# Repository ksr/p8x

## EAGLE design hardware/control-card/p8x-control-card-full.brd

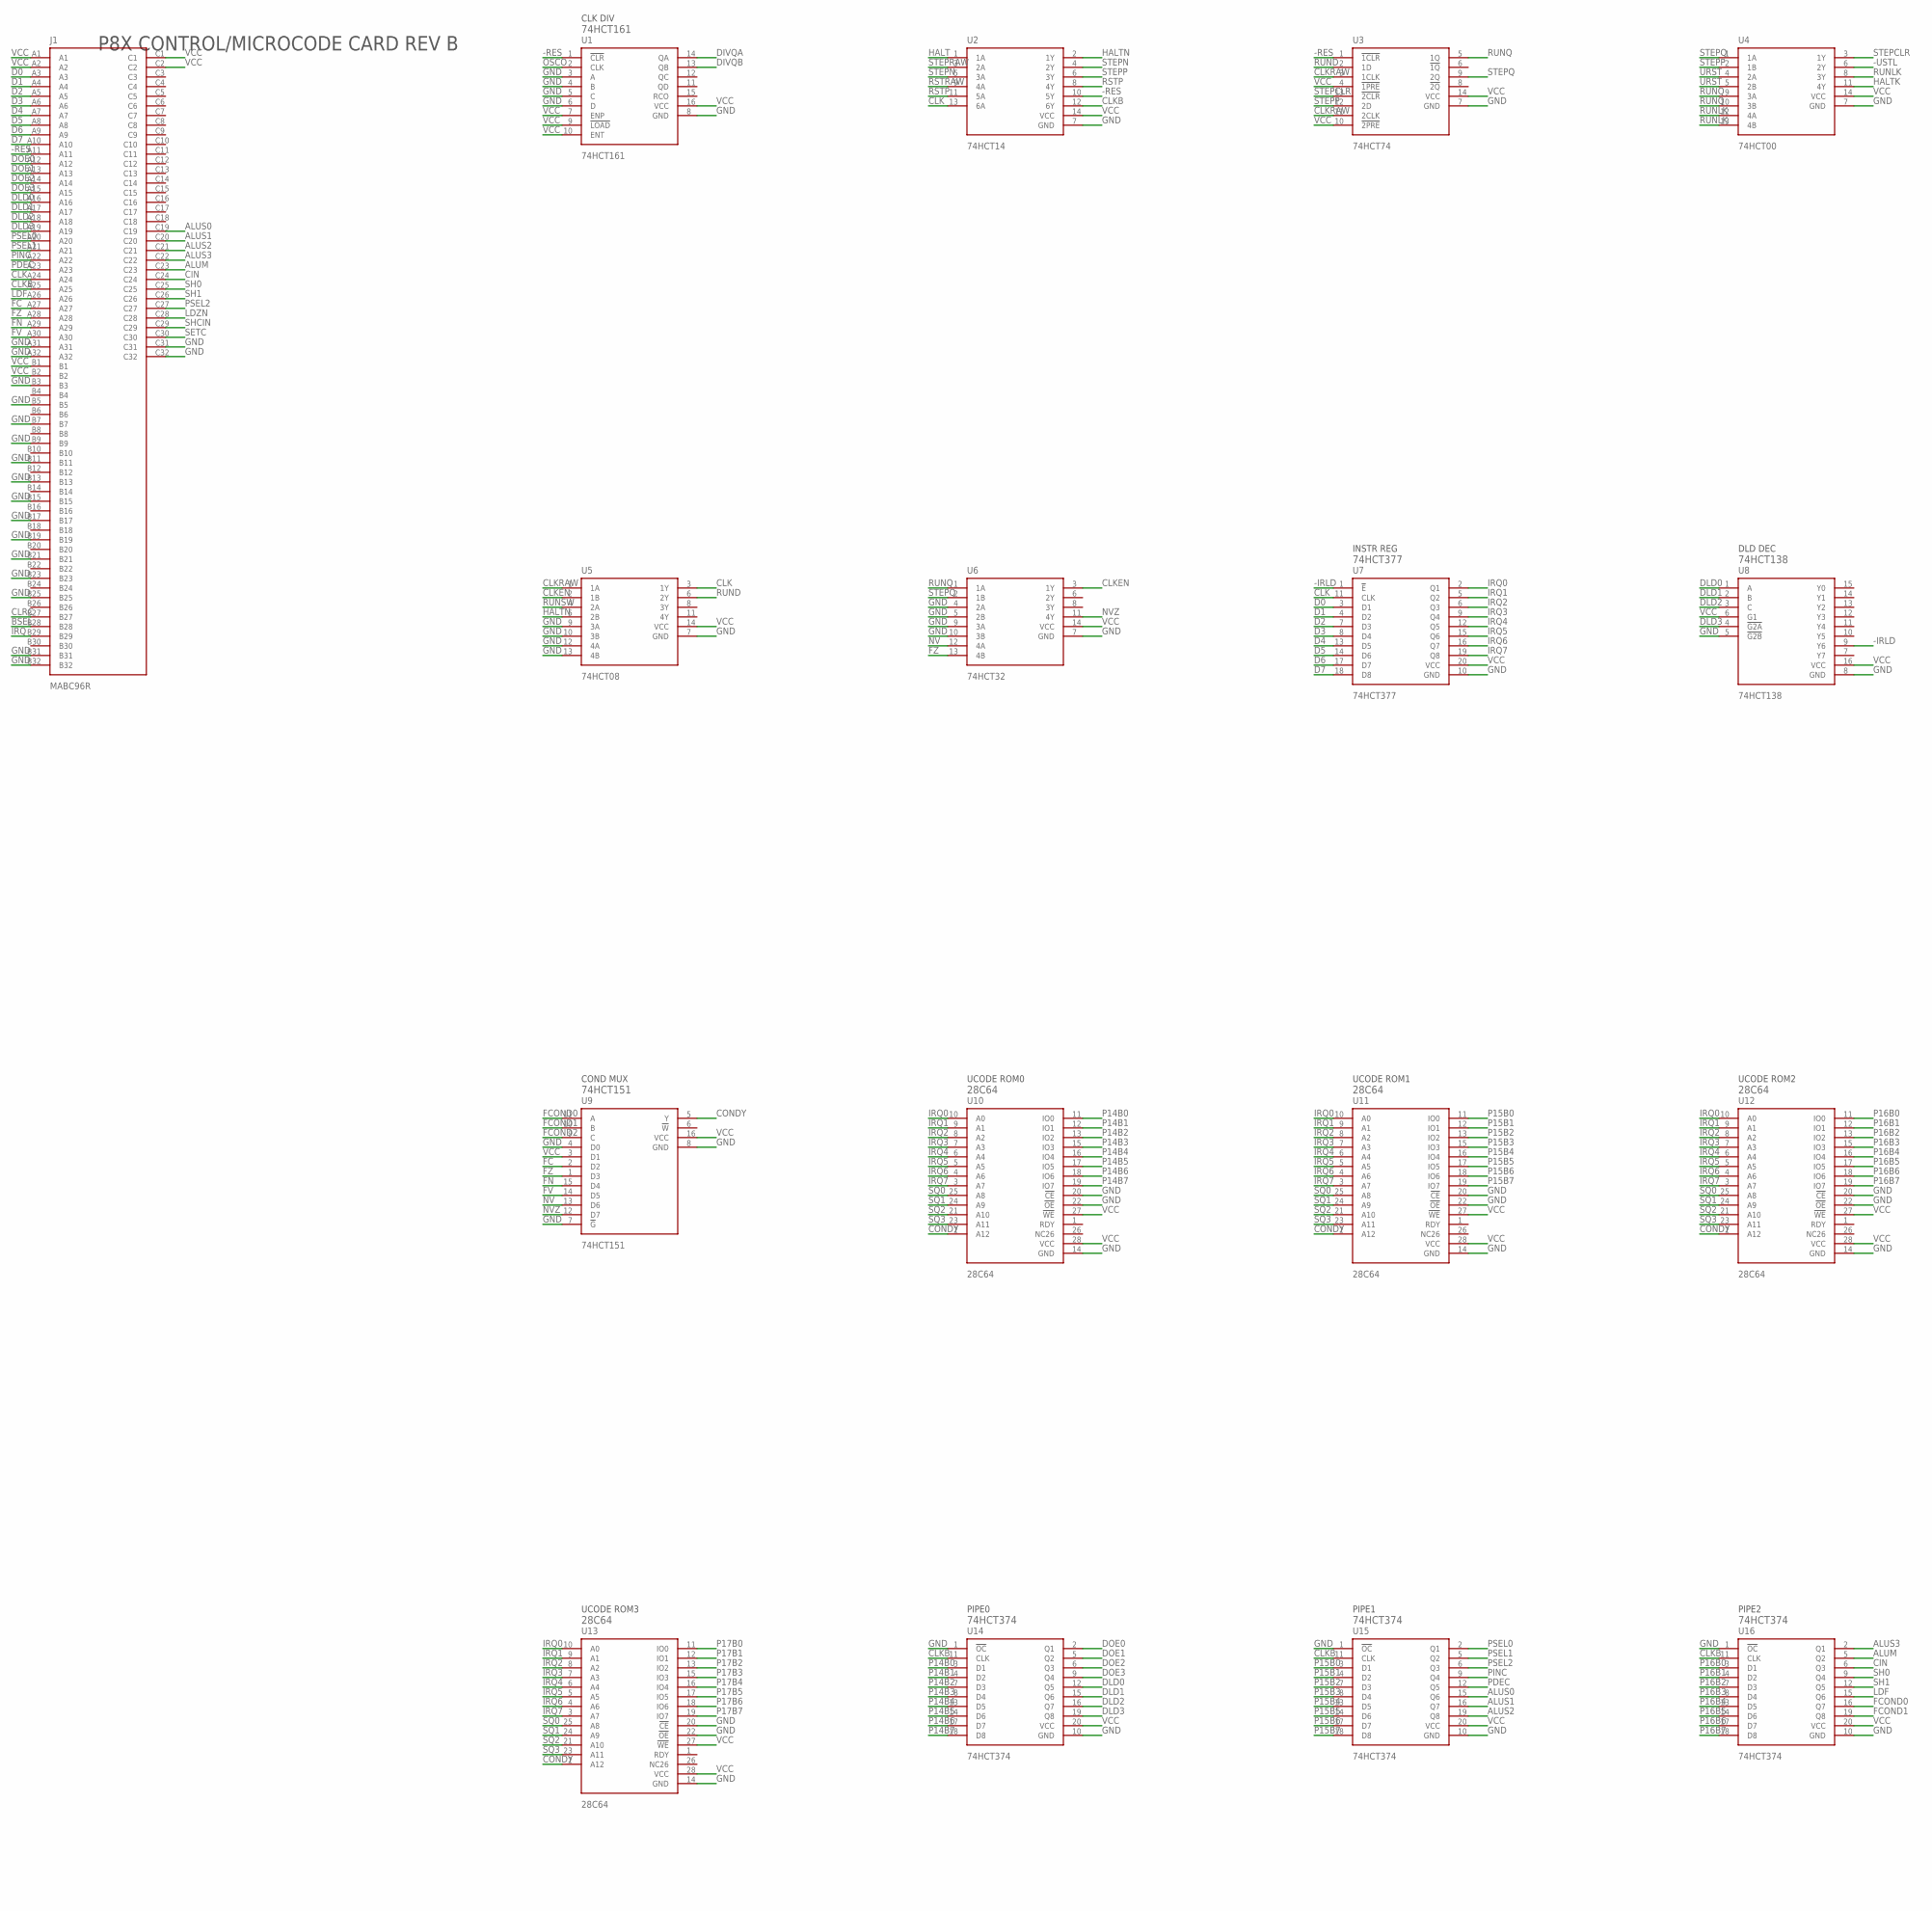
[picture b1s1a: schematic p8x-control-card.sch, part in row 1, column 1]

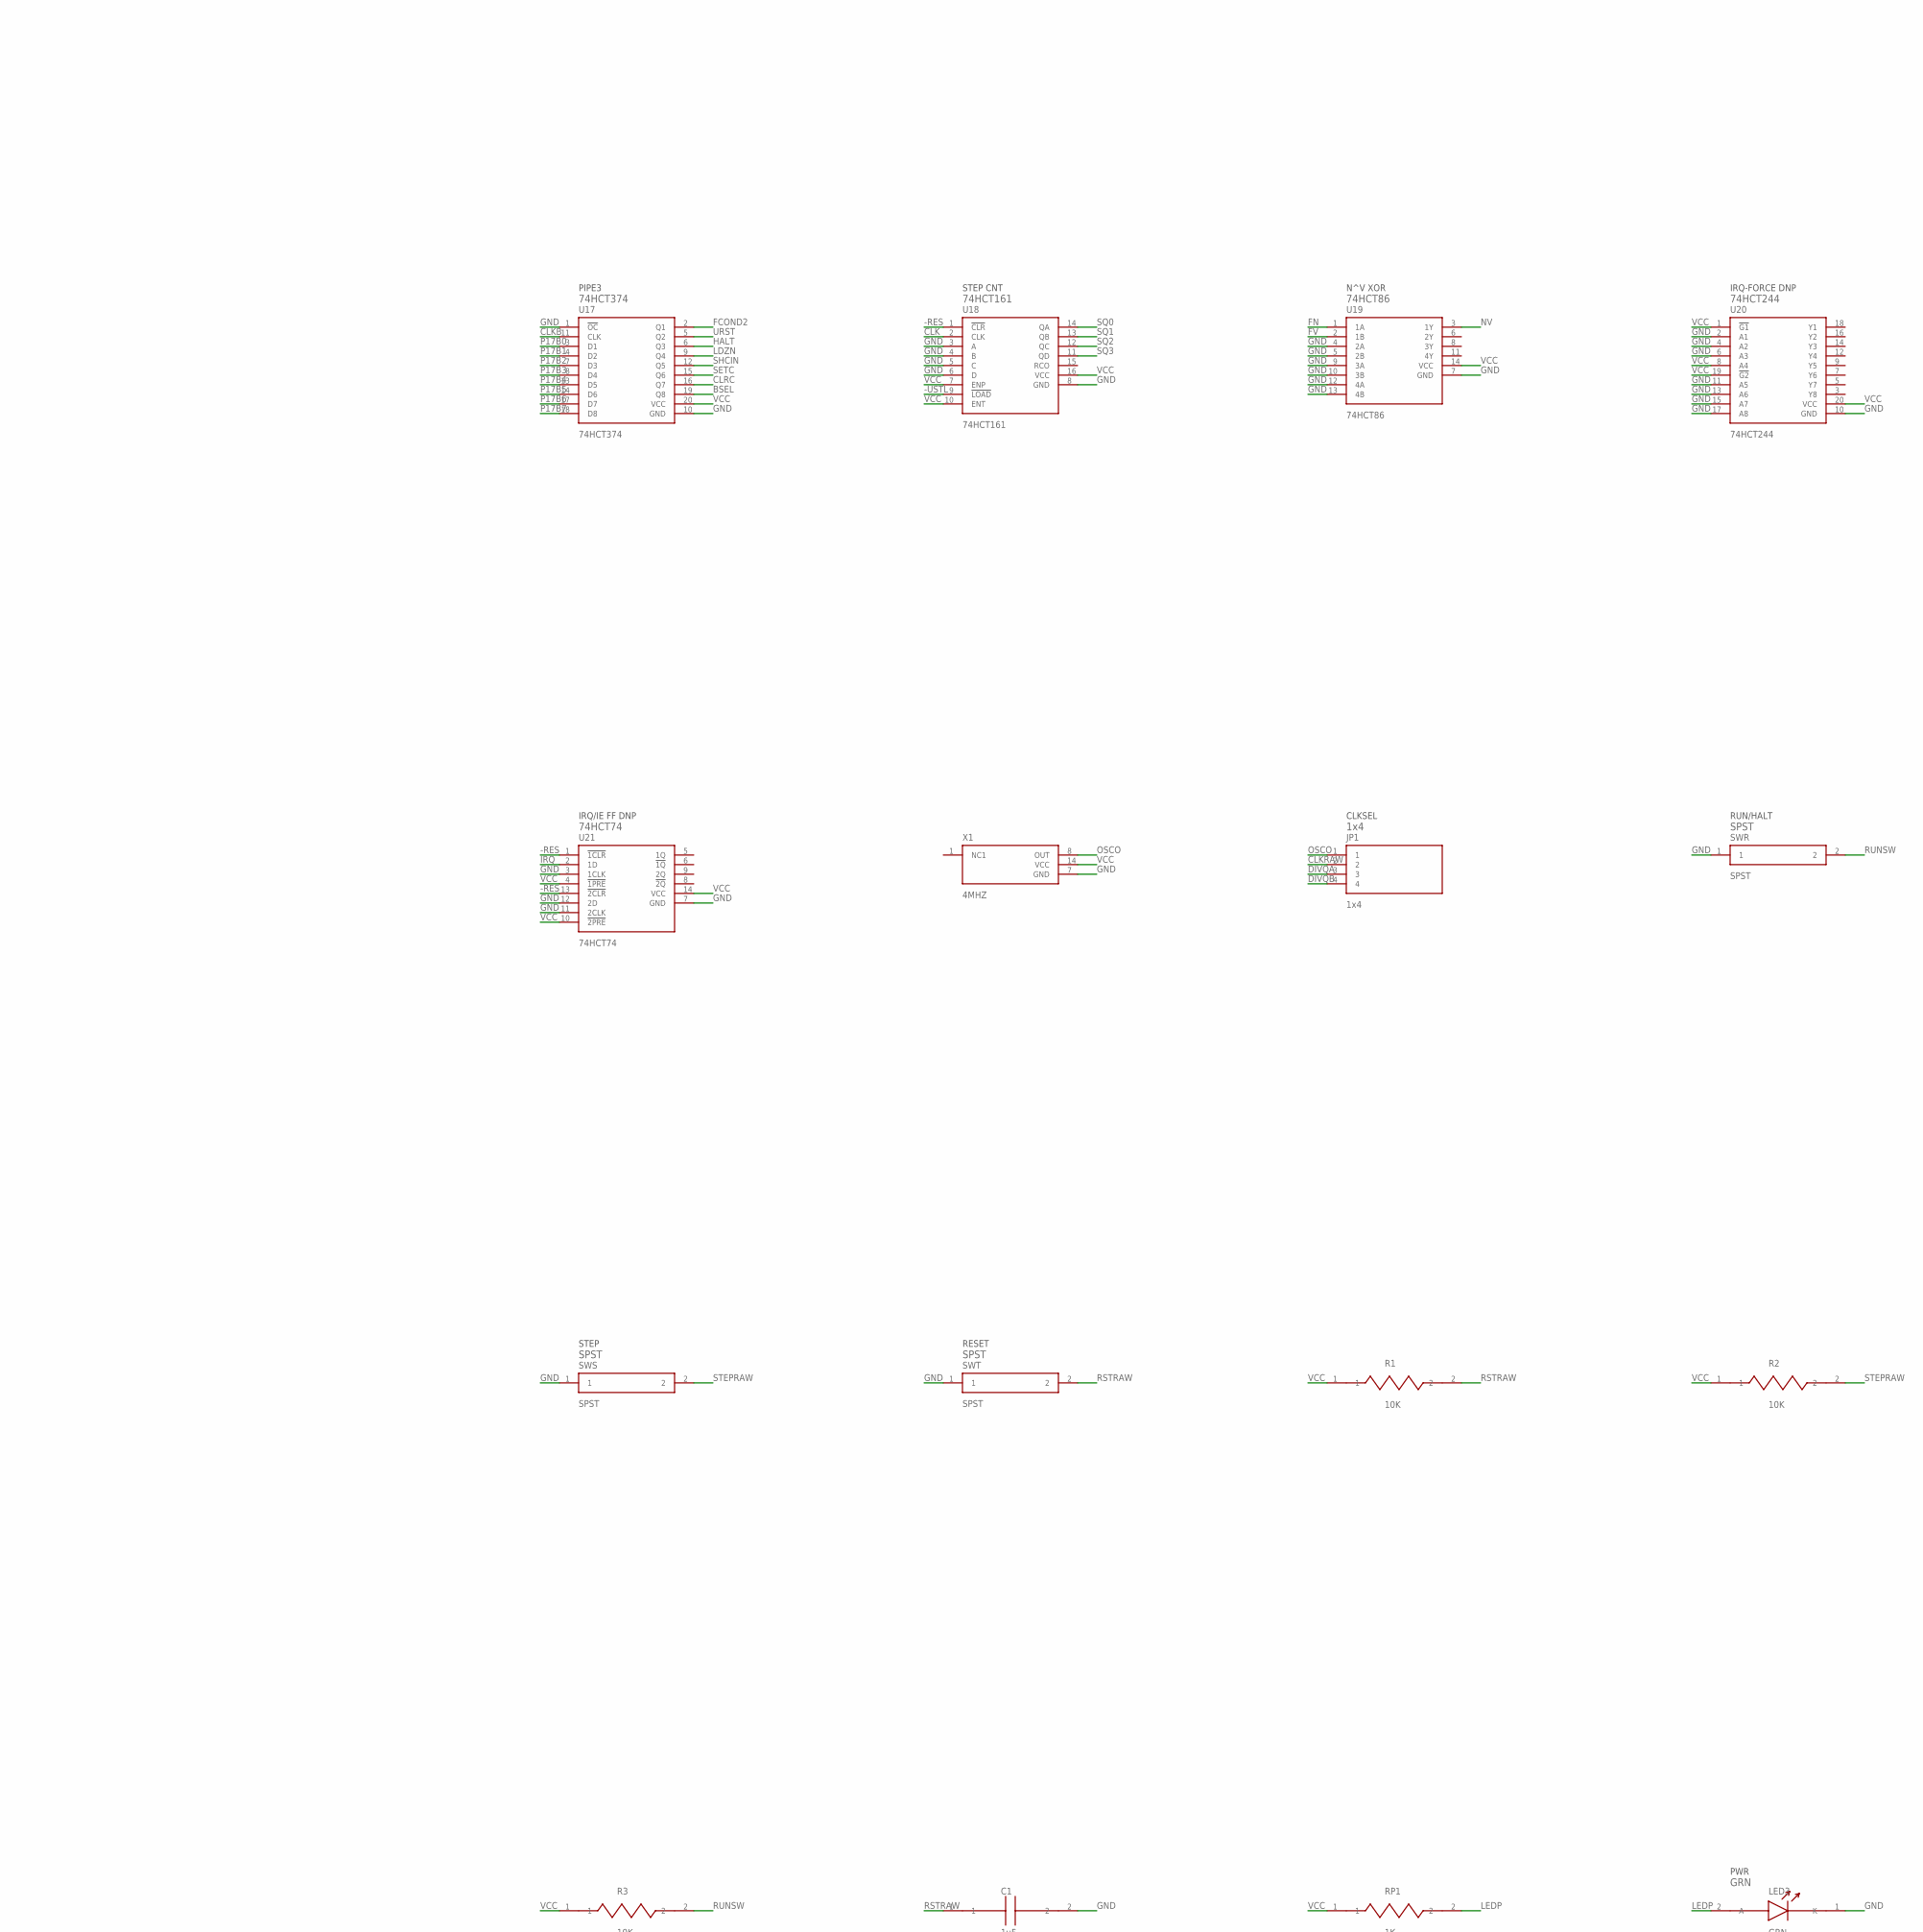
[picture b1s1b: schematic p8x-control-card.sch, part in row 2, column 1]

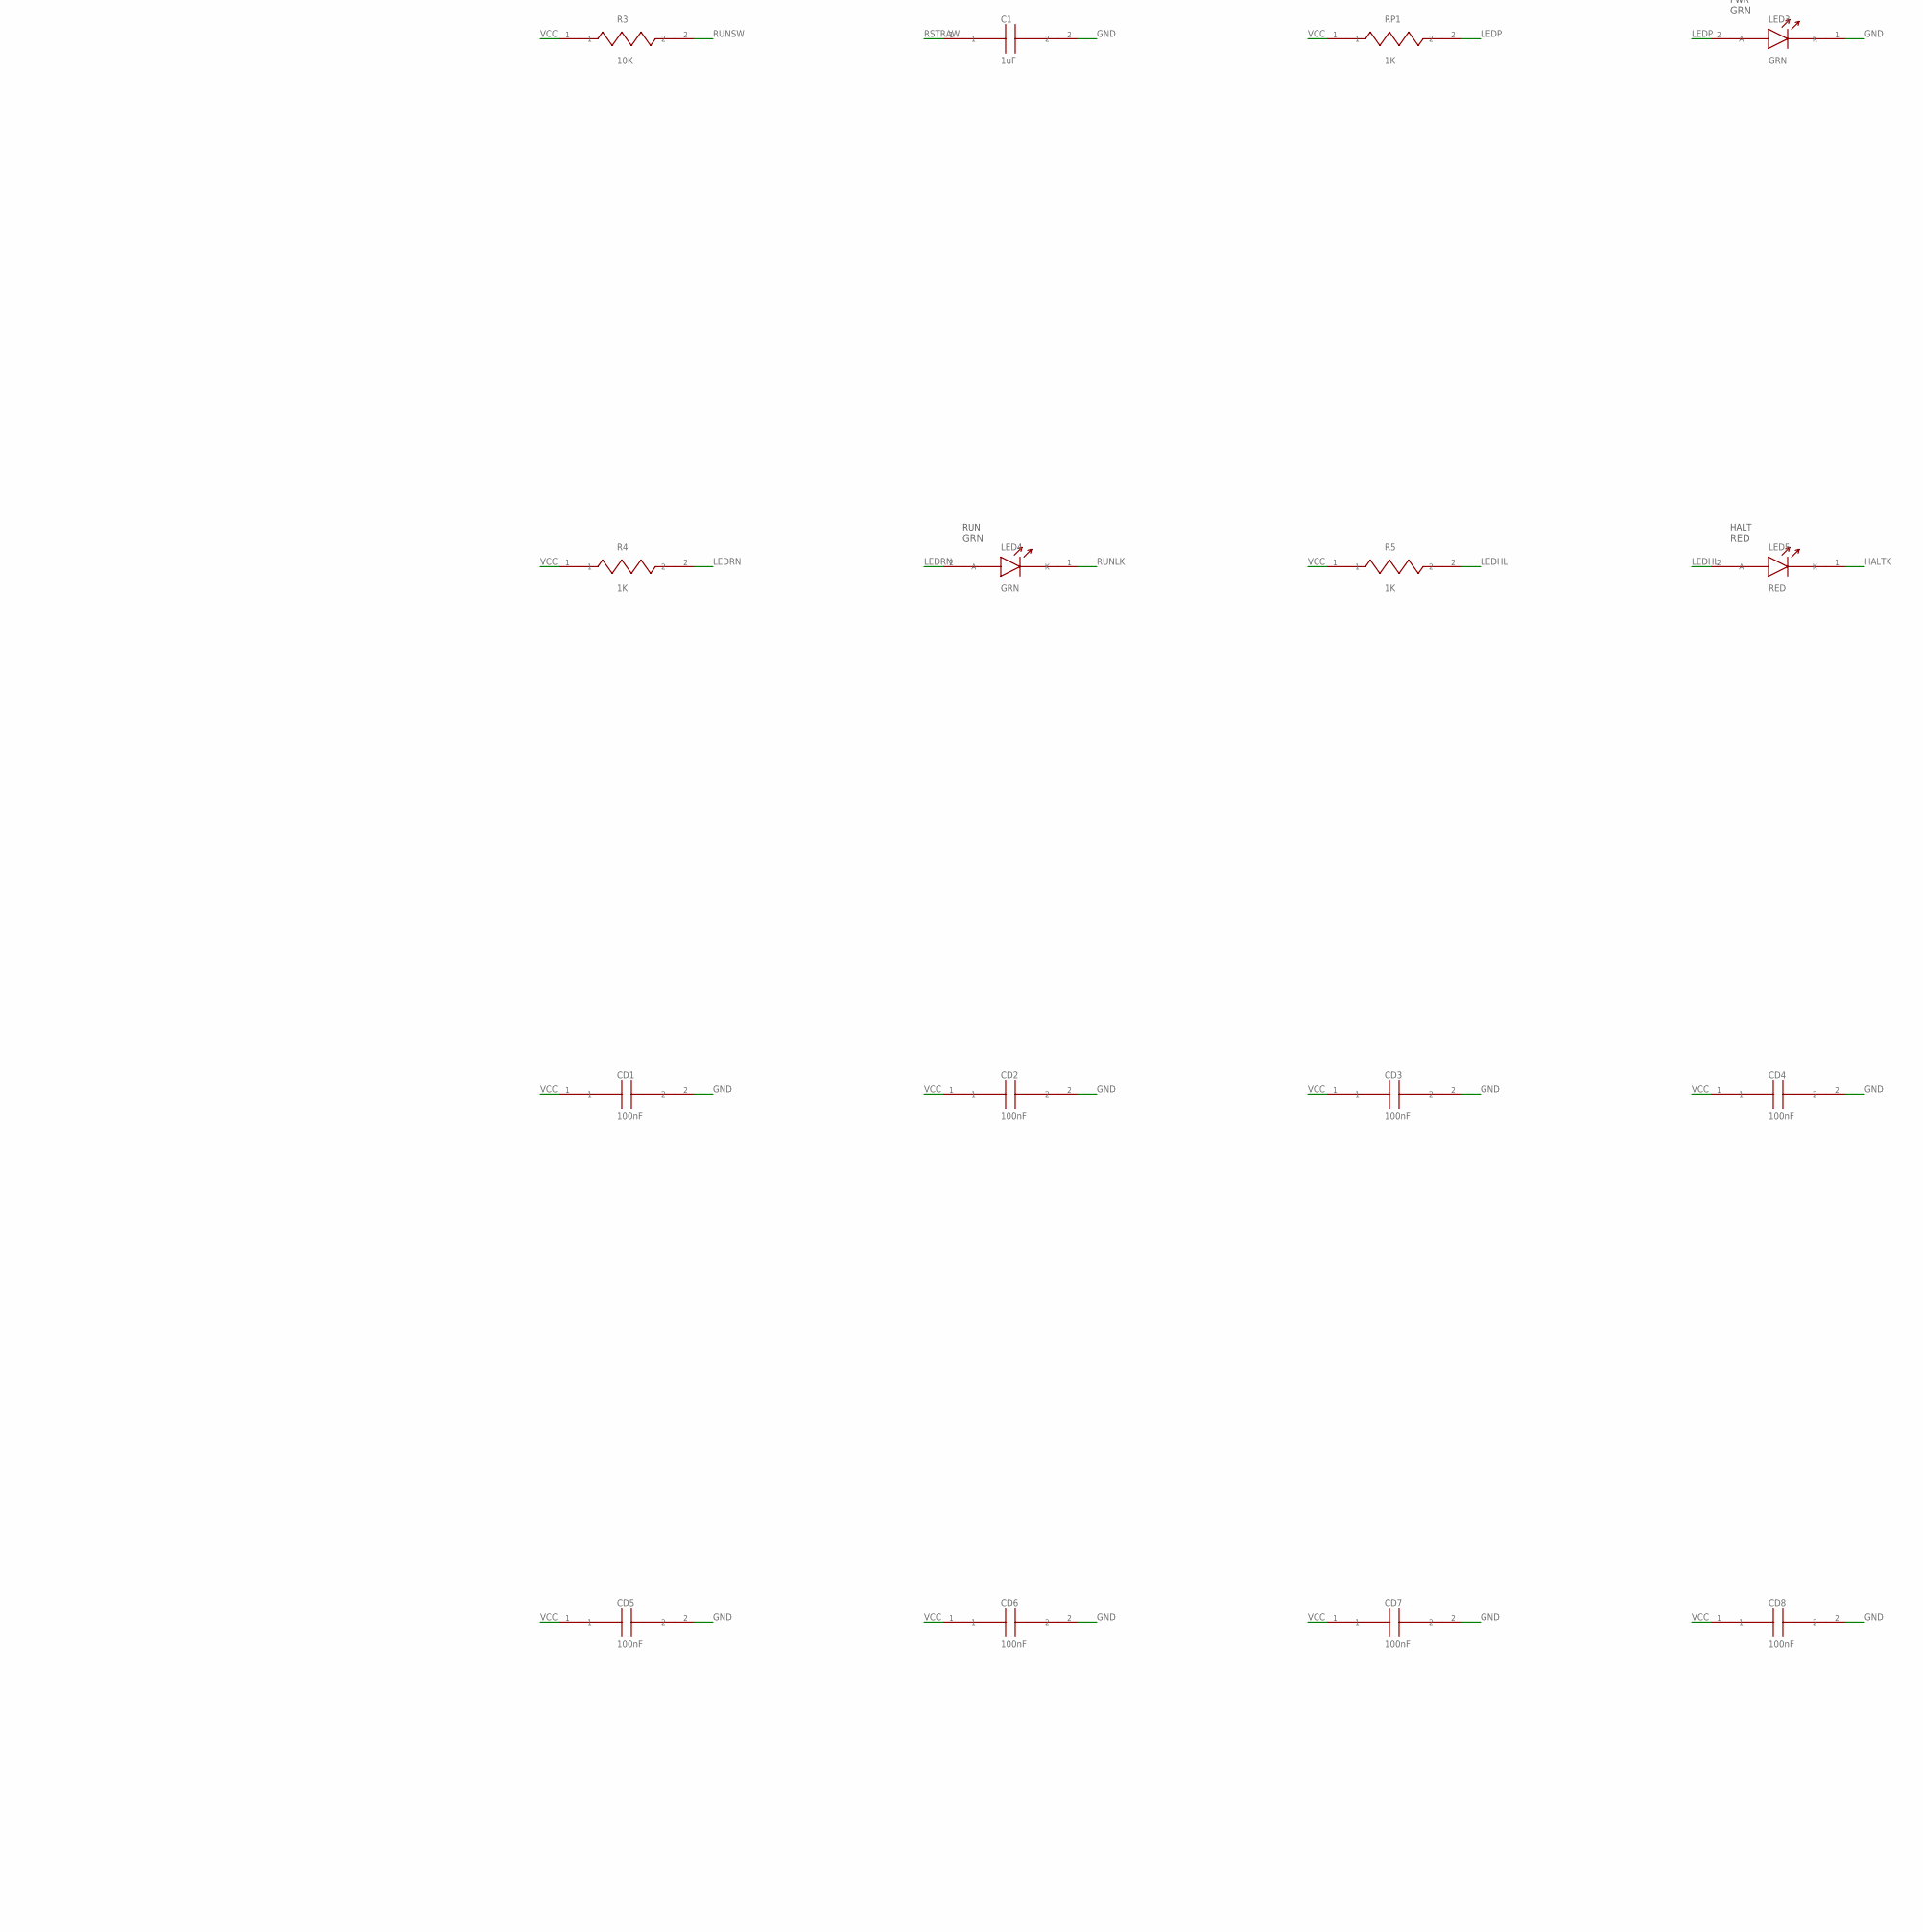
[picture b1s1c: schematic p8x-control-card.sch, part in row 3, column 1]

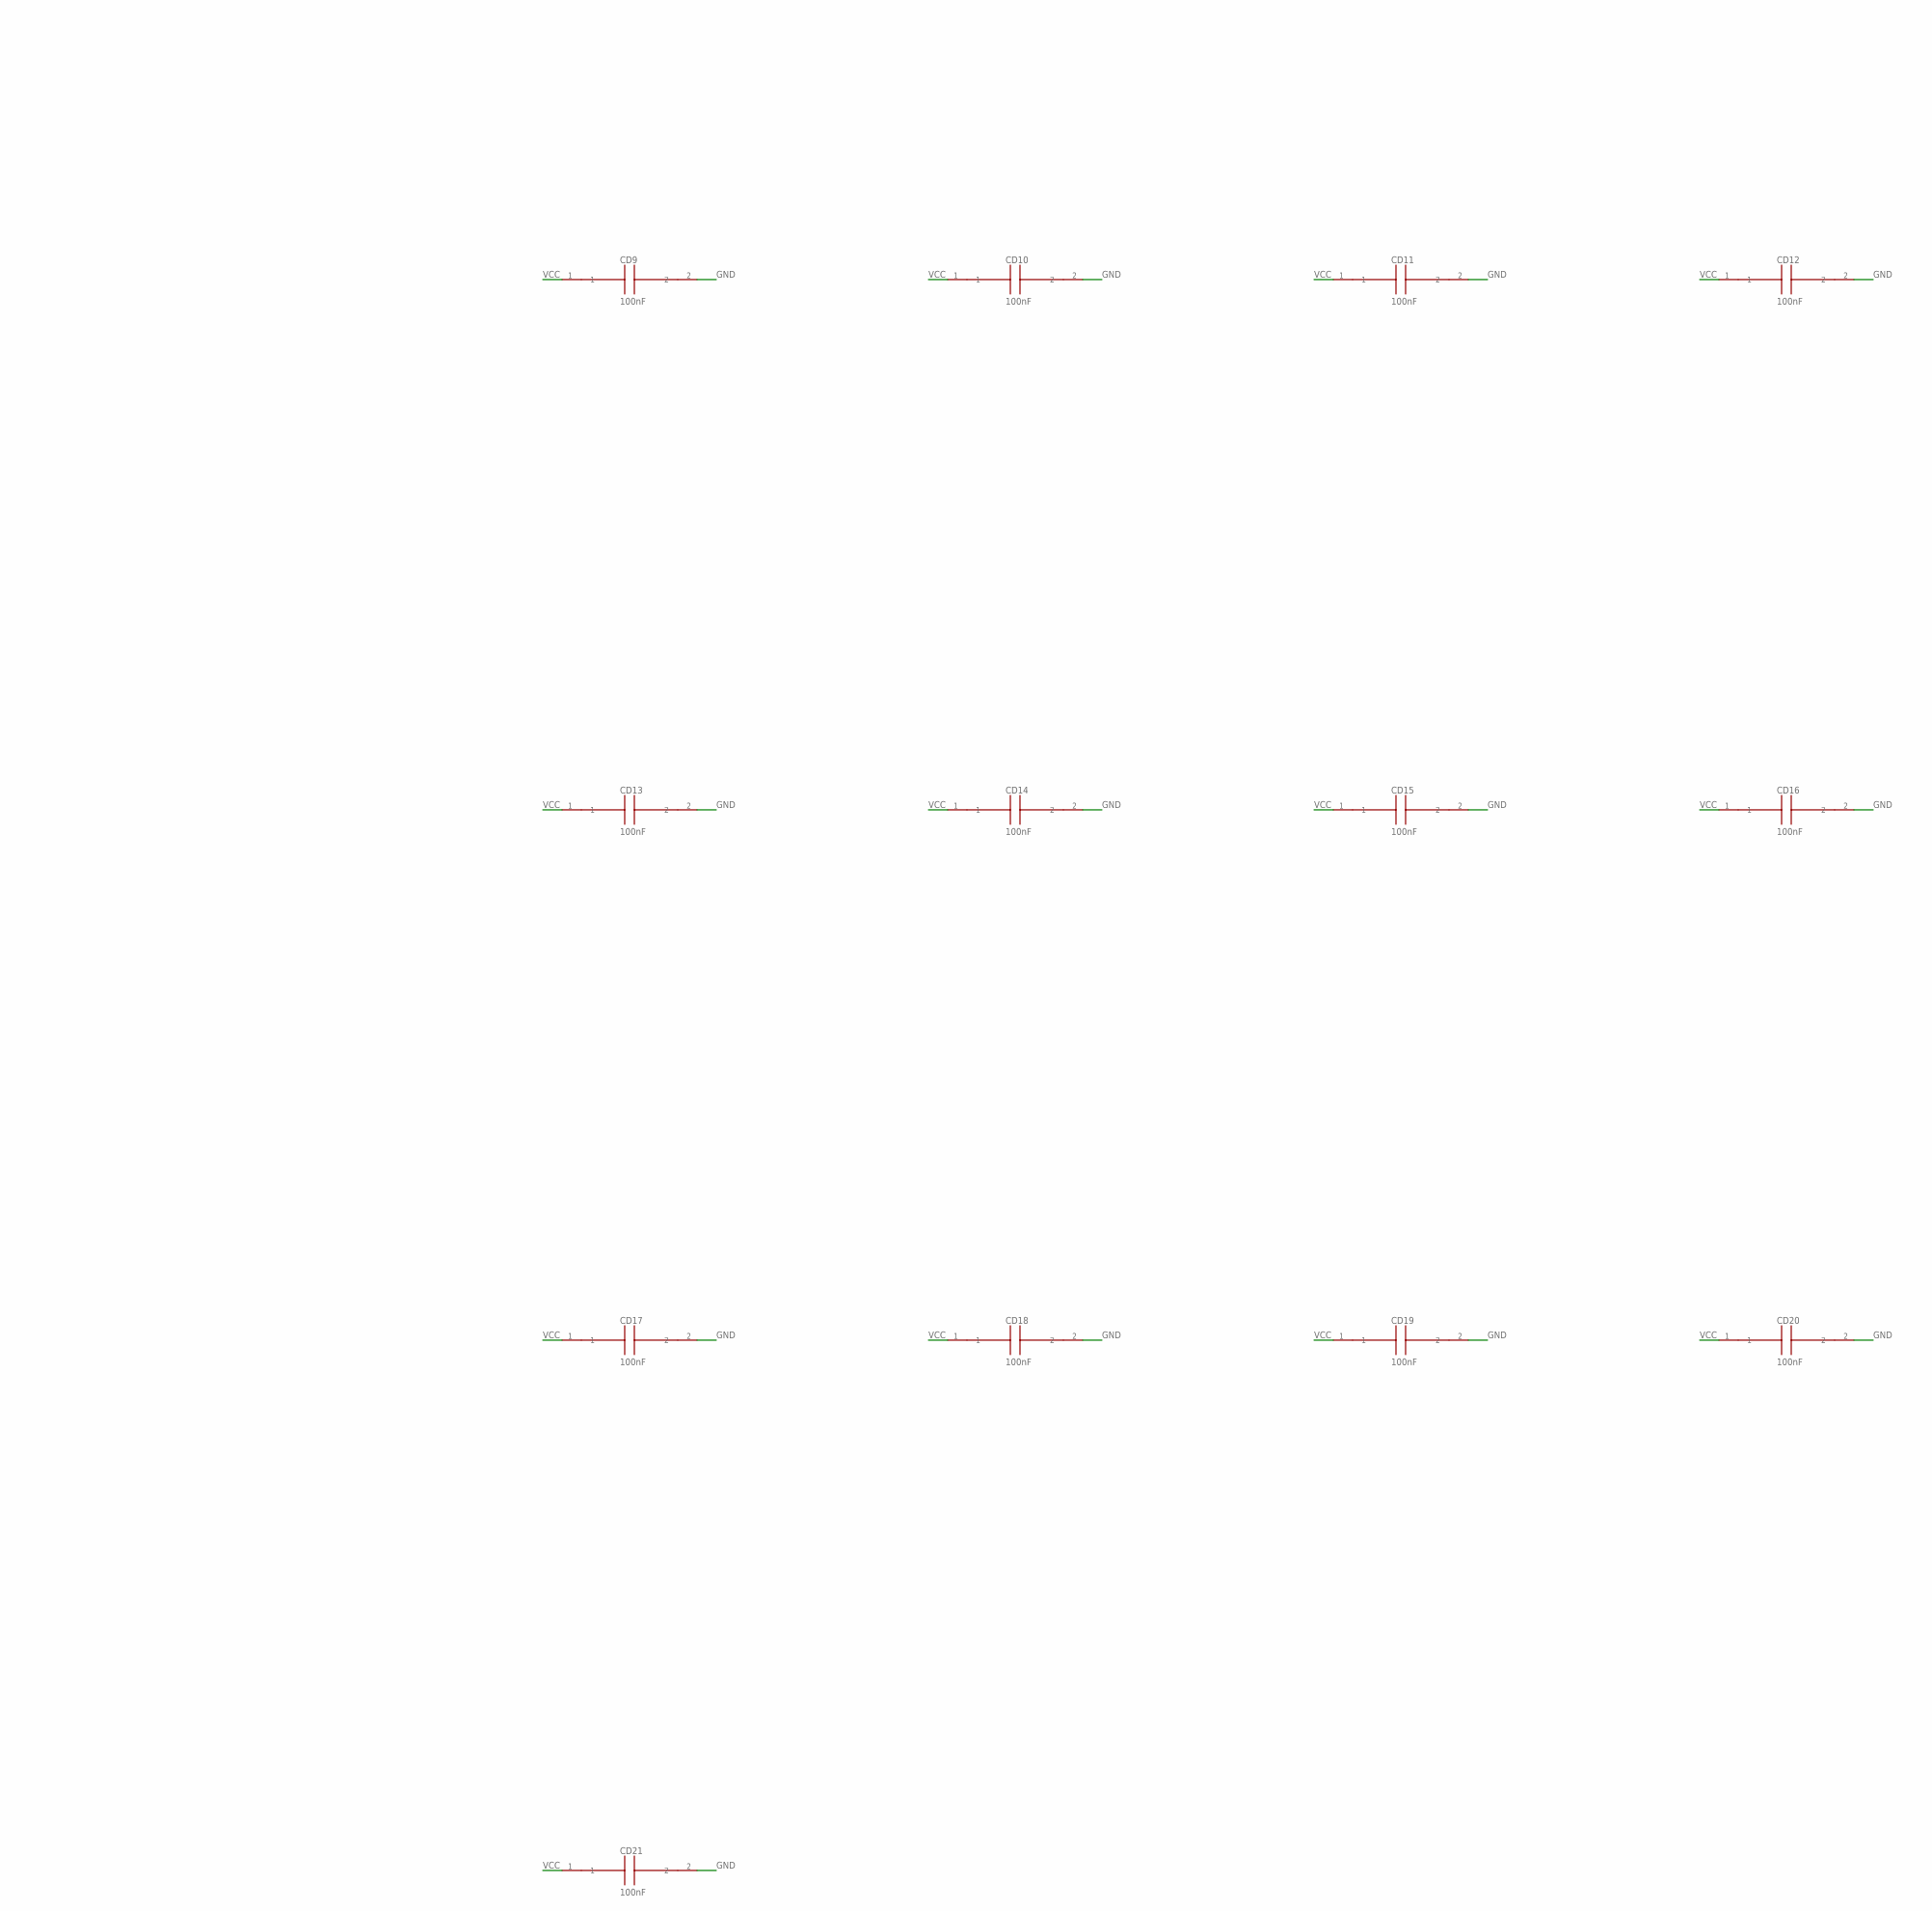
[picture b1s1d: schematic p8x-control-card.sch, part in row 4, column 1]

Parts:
C1: 1uF; C_DISC
CD1, CD2, CD3, CD4, CD5, CD6, CD7, CD8, CD9, CD10, CD11, CD12, CD13, CD14, CD15, CD16, CD17, CD18, CD19, CD20, CD21: 100nF; C_DISC1
J1: MABC96R
JP1: 1x4; HDR4
LED3, LED4: GRN; LED5
LED5: RED; LED5
R1, R2, R3: 10K; R_AXIAL
R4, R5: 1K; R_AXIAL
RP1: 1K; R_AXIAL
SWR: SPST; SW2P
SWS: SPST; SW2P
SWT: SPST; SW2P
U1, U18: 74HCT161; DIP16
U2: 74HCT14; DIP14
U3, U21: 74HCT74; DIP14
U4: 74HCT00; DIP14
U5: 74HCT08; DIP14
U6: 74HCT32; DIP14
U7: 74HCT377; DIP20
U8: 74HCT138; DIP16
U9: 74HCT151; DIP16
U10, U11, U12, U13: 28C64; DIP28W
U14, U15, U16, U17: 74HCT374; DIP20
U19: 74HCT86; DIP14
U20: 74HCT244; DIP20
X1: 4MHZ; OSC4

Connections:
-IRLD: U7.1 (!E), U8.9 (Y6)
-RES: J1.A11, U1.1 (!CLR), U2.10 (5Y), U3.1 (!1CLR), U18.1 (!CLR), U21.1 (!1CLR), U21.13 (!2CLR)
-USTL: U4.6 (2Y), U18.9 (!LOAD)
ALUM: J1.C23, U16.5 (Q2)
ALUS0: J1.C19, U15.15 (Q6)
ALUS1: J1.C20, U15.16 (Q7)
ALUS2: J1.C21, U15.19 (Q8)
ALUS3: J1.C22, U16.2 (Q1)
BSEL: J1.B28, U17.19 (Q8)
CIN: J1.C24, U16.6 (Q3)
CLK: J1.A24, U2.13 (6A), U5.3 (1Y), U7.11 (CLK), U18.2 (CLK)
CLKB: J1.A25, U2.12 (6Y), U14.11 (CLK), U15.11 (CLK), U16.11 (CLK), U17.11 (CLK)
CLKEN: U5.2 (1B), U6.3 (1Y)
CLKRAW: JP1.2, U3.3 (1CLK), U3.11 (2CLK), U5.1 (1A)
CLRC: J1.B27, U17.16 (Q7)
CONDY: U9.5 (Y), U10.2 (A12), U11.2 (A12), U12.2 (A12), U13.2 (A12)
D0: J1.A3, U7.3 (D1)
D1: J1.A4, U7.4 (D2)
D2: J1.A5, U7.7 (D3)
D3: J1.A6, U7.8 (D4)
D4: J1.A7, U7.13 (D5)
D5: J1.A8, U7.14 (D6)
D6: J1.A9, U7.17 (D7)
D7: J1.A10, U7.18 (D8)
DIVQA: JP1.3, U1.14 (QA)
DIVQB: JP1.4, U1.13 (QB)
DLD0: J1.A16, U8.1 (A), U14.12 (Q5)
DLD1: J1.A17, U8.2 (B), U14.15 (Q6)
DLD2: J1.A18, U8.3 (C), U14.16 (Q7)
DLD3: J1.A19, U8.4 (!G2A), U14.19 (Q8)
DOE0: J1.A12, U14.2 (Q1)
DOE1: J1.A13, U14.5 (Q2)
DOE2: J1.A14, U14.6 (Q3)
DOE3: J1.A15, U14.9 (Q4)
FC: J1.A27, U9.2 (D2)
FCOND0: U9.11 (A), U16.16 (Q7)
FCOND1: U9.10 (B), U16.19 (Q8)
FCOND2: U9.9 (C), U17.2 (Q1)
FN: J1.A29, U9.15 (D4), U19.1 (1A)
FV: J1.A30, U9.14 (D5), U19.2 (1B)
FZ: J1.A28, U6.13 (4B), U9.1 (D3)
GND: C1.2, CD1.2, CD2.2, CD3.2, CD4.2, CD5.2, CD6.2, CD7.2, CD8.2, CD9.2, CD10.2, CD11.2, CD12.2, CD13.2, CD14.2, CD15.2, CD16.2, CD17.2, CD18.2, CD19.2, CD20.2, CD21.2, J1.A31, J1.A32, J1.B3, J1.B5, J1.B7, J1.B9, J1.B11, J1.B13, J1.B15, J1.B17, J1.B19, J1.B21, J1.B23, J1.B25, J1.B31, J1.B32, J1.C31, J1.C32, LED3.1 (K), SWR.1, SWS.1, SWT.1, U1.3 (A), U1.4 (B), U1.5 (C), U1.6 (D), U1.8 (GND), U2.7 (GND), U3.7 (GND), U4.7 (GND), U5.7 (GND), U5.9 (3A), U5.10 (3B), U5.12 (4A), U5.13 (4B), U6.4 (2A), U6.5 (2B), U6.7 (GND), U6.9 (3A), U6.10 (3B), U7.10 (GND), U8.5 (!G2B), U8.8 (GND), U9.4 (D0), U9.7 (!G), U9.8 (GND), U10.14 (GND), U10.20 (!CE), U10.22 (!OE), U11.14 (GND), U11.20 (!CE), U11.22 (!OE), U12.14 (GND), U12.20 (!CE), U12.22 (!OE), U13.14 (GND), U13.20 (!CE), U13.22 (!OE), U14.1 (!OC), U14.10 (GND), U15.1 (!OC), U15.10 (GND), U16.1 (!OC), U16.10 (GND), U17.1 (!OC), U17.10 (GND), U18.3 (A), U18.4 (B), U18.5 (C), U18.6 (D), U18.8 (GND), U19.4 (2A), U19.5 (2B), U19.7 (GND), U19.9 (3A), U19.10 (3B), U19.12 (4A), U19.13 (4B), U20.2 (A1), U20.4 (A2), U20.6 (A3), U20.10 (GND), U20.11 (A5), U20.13 (A6), U20.15 (A7), U20.17 (A8), U21.3 (1CLK), U21.7 (GND), U21.11 (2CLK), U21.12 (2D), X1.7 (GND)
HALT: U2.1 (1A), U17.6 (Q3)
HALTK: LED5.1 (K), U4.11 (4Y)
HALTN: U2.2 (1Y), U5.5 (2B)
IRQ: J1.B29, U21.2 (1D)
IRQ0: U7.2 (Q1), U10.10 (A0), U11.10 (A0), U12.10 (A0), U13.10 (A0)
IRQ1: U7.5 (Q2), U10.9 (A1), U11.9 (A1), U12.9 (A1), U13.9 (A1)
IRQ2: U7.6 (Q3), U10.8 (A2), U11.8 (A2), U12.8 (A2), U13.8 (A2)
IRQ3: U7.9 (Q4), U10.7 (A3), U11.7 (A3), U12.7 (A3), U13.7 (A3)
IRQ4: U7.12 (Q5), U10.6 (A4), U11.6 (A4), U12.6 (A4), U13.6 (A4)
IRQ5: U7.15 (Q6), U10.5 (A5), U11.5 (A5), U12.5 (A5), U13.5 (A5)
IRQ6: U7.16 (Q7), U10.4 (A6), U11.4 (A6), U12.4 (A6), U13.4 (A6)
IRQ7: U7.19 (Q8), U10.3 (A7), U11.3 (A7), U12.3 (A7), U13.3 (A7)
LDF: J1.A26, U16.15 (Q6)
LDZN: J1.C28, U17.9 (Q4)
LEDHL: LED5.2 (A), R5.2
LEDP: LED3.2 (A), RP1.2
LEDRN: LED4.2 (A), R4.2
NV: U6.12 (4A), U9.13 (D6), U19.3 (1Y)
NVZ: U6.11 (4Y), U9.12 (D7)
OSCO: JP1.1, U1.2 (CLK), X1.8 (OUT)
P14B0: U10.11 (IO0), U14.3 (D1)
P14B1: U10.12 (IO1), U14.4 (D2)
P14B2: U10.13 (IO2), U14.7 (D3)
P14B3: U10.15 (IO3), U14.8 (D4)
P14B4: U10.16 (IO4), U14.13 (D5)
P14B5: U10.17 (IO5), U14.14 (D6)
P14B6: U10.18 (IO6), U14.17 (D7)
P14B7: U10.19 (IO7), U14.18 (D8)
P15B0: U11.11 (IO0), U15.3 (D1)
P15B1: U11.12 (IO1), U15.4 (D2)
P15B2: U11.13 (IO2), U15.7 (D3)
P15B3: U11.15 (IO3), U15.8 (D4)
P15B4: U11.16 (IO4), U15.13 (D5)
P15B5: U11.17 (IO5), U15.14 (D6)
P15B6: U11.18 (IO6), U15.17 (D7)
P15B7: U11.19 (IO7), U15.18 (D8)
P16B0: U12.11 (IO0), U16.3 (D1)
P16B1: U12.12 (IO1), U16.4 (D2)
P16B2: U12.13 (IO2), U16.7 (D3)
P16B3: U12.15 (IO3), U16.8 (D4)
P16B4: U12.16 (IO4), U16.13 (D5)
P16B5: U12.17 (IO5), U16.14 (D6)
P16B6: U12.18 (IO6), U16.17 (D7)
P16B7: U12.19 (IO7), U16.18 (D8)
P17B0: U13.11 (IO0), U17.3 (D1)
P17B1: U13.12 (IO1), U17.4 (D2)
P17B2: U13.13 (IO2), U17.7 (D3)
P17B3: U13.15 (IO3), U17.8 (D4)
P17B4: U13.16 (IO4), U17.13 (D5)
P17B5: U13.17 (IO5), U17.14 (D6)
P17B6: U13.18 (IO6), U17.17 (D7)
P17B7: U13.19 (IO7), U17.18 (D8)
PDEC: J1.A23, U15.12 (Q5)
PINC: J1.A22, U15.9 (Q4)
PSEL0: J1.A20, U15.2 (Q1)
PSEL1: J1.A21, U15.5 (Q2)
PSEL2: J1.C27, U15.6 (Q3)
RSTP: U2.8 (4Y), U2.11 (5A)
RSTRAW: C1.1, R1.2, SWT.2, U2.9 (4A)
RUND: U3.2 (1D), U5.6 (2Y)
RUNLK: LED4.1 (K), U4.8 (3Y), U4.12 (4A), U4.13 (4B)
RUNQ: U3.5 (1Q), U4.9 (3A), U4.10 (3B), U6.1 (1A)
RUNSW: R3.2, SWR.2, U5.4 (2A)
SETC: J1.C30, U17.15 (Q6)
SH0: J1.C25, U16.9 (Q4)
SH1: J1.C26, U16.12 (Q5)
SHCIN: J1.C29, U17.12 (Q5)
SQ0: U10.25 (A8), U11.25 (A8), U12.25 (A8), U13.25 (A8), U18.14 (QA)
SQ1: U10.24 (A9), U11.24 (A9), U12.24 (A9), U13.24 (A9), U18.13 (QB)
SQ2: U10.21 (A10), U11.21 (A10), U12.21 (A10), U13.21 (A10), U18.12 (QC)
SQ3: U10.23 (A11), U11.23 (A11), U12.23 (A11), U13.23 (A11), U18.11 (QD)
STEPCLR: U3.13 (!2CLR), U4.3 (1Y)
STEPN: U2.4 (2Y), U2.5 (3A)
STEPP: U2.6 (3Y), U3.12 (2D), U4.2 (1B)
STEPQ: U3.9 (2Q), U4.1 (1A), U6.2 (1B)
STEPRAW: R2.2, SWS.2, U2.3 (2A)
URST: U4.4 (2A), U4.5 (2B), U17.5 (Q2)
VCC: CD1.1, CD2.1, CD3.1, CD4.1, CD5.1, CD6.1, CD7.1, CD8.1, CD9.1, CD10.1, CD11.1, CD12.1, CD13.1, CD14.1, CD15.1, CD16.1, CD17.1, CD18.1, CD19.1, CD20.1, CD21.1, J1.A1, J1.A2, J1.B1, J1.B2, J1.C1, J1.C2, R1.1, R2.1, R3.1, R4.1, R5.1, RP1.1, U1.7 (ENP), U1.9 (!LOAD), U1.10 (ENT), U1.16 (VCC), U2.14 (VCC), U3.4 (!1PRE), U3.10 (!2PRE), U3.14 (VCC), U4.14 (VCC), U5.14 (VCC), U6.14 (VCC), U7.20 (VCC), U8.6 (G1), U8.16 (VCC), U9.3 (D1), U9.16 (VCC), U10.27 (!WE), U10.28 (VCC), U11.27 (!WE), U11.28 (VCC), U12.27 (!WE), U12.28 (VCC), U13.27 (!WE), U13.28 (VCC), U14.20 (VCC), U15.20 (VCC), U16.20 (VCC), U17.20 (VCC), U18.7 (ENP), U18.10 (ENT), U18.16 (VCC), U19.14 (VCC), U20.1 (!G1), U20.8 (A4), U20.19 (!G2), U20.20 (VCC), U21.4 (!1PRE), U21.10 (!2PRE), U21.14 (VCC), X1.14 (VCC)

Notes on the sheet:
P8X CONTROL/MICROCODE CARD REV B
N^V XOR
74HCT86
CLK DIV
74HCT161
INSTR REG
74HCT377
DLD DEC
74HCT138
COND MUX
74HCT151
UCODE ROM0
28C64
UCODE ROM1
UCODE ROM2
UCODE ROM3
PIPE0
74HCT374
PIPE1
PIPE2
PIPE3
STEP CNT
IRQ-FORCE DNP
74HCT244
IRQ/IE FF DNP
74HCT74
CLKSEL
1x4
RUN/HALT
SPST
STEP
RESET
PWR
GRN
RUN
HALT
RED

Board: 4 copper layers, 58 parts (0 on the bottom side), 120 nets, no tracks yet.
